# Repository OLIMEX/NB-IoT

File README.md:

# NB-IoT
NB-IoT is LPWAN technology for IoT with many advantages over LoRa and SigFox.

NB-IoT technology works over existing GSM network. This means all existing GSM networks with LTE can support NB-IoT if the protocol is installed by your GSM operator.
One base cell can talk up to 100 000 NB-IoT nodes. One base cell can establish connection in urban area 1-10km and in rural area 10-100km
One NB-IoT node can last on battery up to 10 years if less 200 bytes per day are transmitted

# NB-IoT-DevKit board has these features:
- BC-66 all world wide GSM bands coverage
- NB-IoT 25.5 kbps up and down link
- Ultra low power design
- Build in Li-Po battery charger
- Nano SIM
- Level shifters for 5x GPIOs, I2C, SPI, UART
- Micro UEXT connector
- U.FL antenna connector
- Status LEDs
- Dimensions 40x25 mm

# License
- Hardware is with CERN OHL v1.2 license
- Software is with GPL3 license
- Documentation is with CC BY-SA 4.0 license

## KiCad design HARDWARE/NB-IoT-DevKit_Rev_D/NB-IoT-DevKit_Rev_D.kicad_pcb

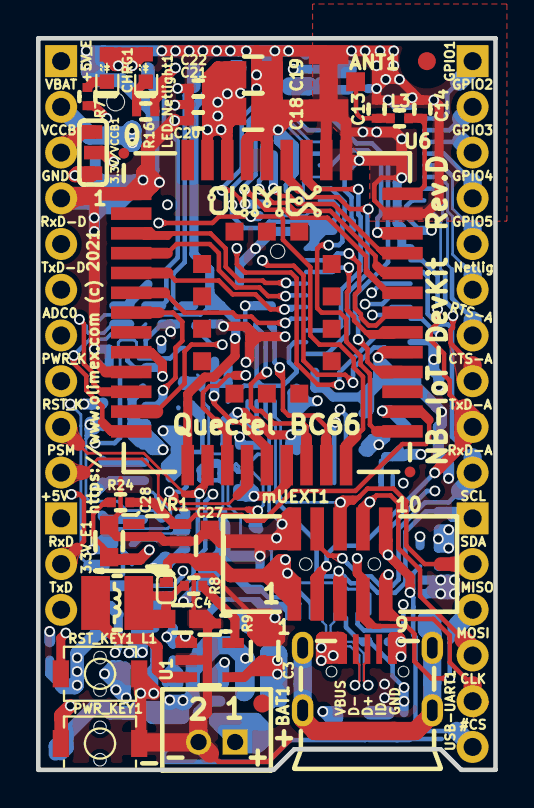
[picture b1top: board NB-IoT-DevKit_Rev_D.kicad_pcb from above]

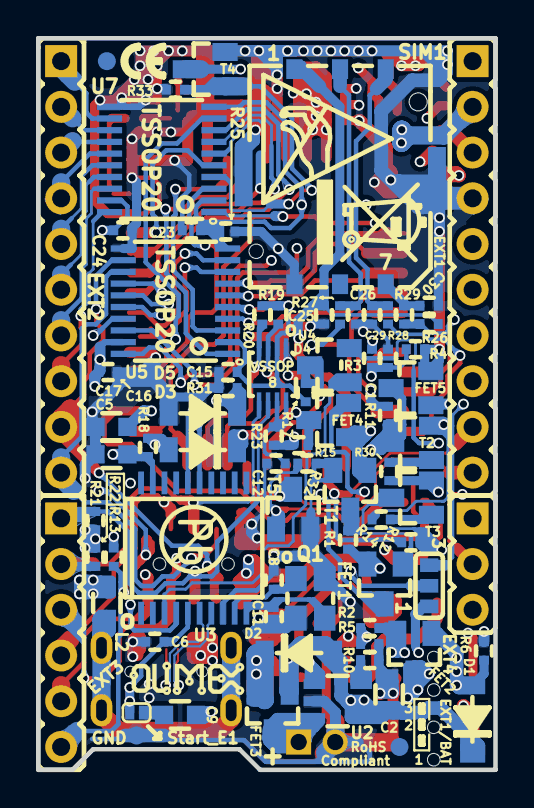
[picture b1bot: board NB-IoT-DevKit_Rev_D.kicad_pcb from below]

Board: 4 copper layers, 25.4 x 40.6 mm, 116 parts (82 on the bottom side), 93 nets.

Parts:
3.3V/VCCB1: Soldered/Opened; SJ_2_SMALL
3.3V_E1: Soldered; SJ_1_SMALLER
ANT1: U.FL-R-SMT-1
BAT1: DW02S; LIPO_BAT_VERTICAL_DW02S
BAT/EXT1: BAT:Soldered/EXT:Opened; SJ_2_SMALL
C1: 1nF/50V/10%/X7R/C0402; C_0402_5MIL_DWS
C2, C3, C4, C5, C9, C27, C28: 22uF/6.3V/20%/X5R/C0603; C_0603_5MIL_DWS
C6, C12, C15, C16, C20, C23, C24, C25: 100nF/10V/10%/X5R/C0402; C_0402_5MIL_DWS
C8, C11: 27pF/50V/5%/C0G/C0402; C_0402_5MIL_DWS
C13, C14, C22: NA/C0402; C_0402_5MIL_DWS
C17: 4.7uF/6.3V/20%/X5R/C0603; C_0603_5MIL_DWS
C18, C19: 47uF/6.3V/20%/X5R/C0805; C_0805_5MIL_DWS
C21, C26, C29, C30: 33pF/50V/5%/COG/C0402; C_0402_5MIL_DWS
CHRG1: LED/YELLOW/0603; LED_0603_KA
D1, D2, D3, D5: 1N5819S4/SOD123; SOD-123_1C-2A_KA
D4: BAT54A(SOT23-3); SOT23-3
EXT1, EXT2: HN1x10
EXT3: HN1x6
EXT4: HN1x3
FET1, FET2, FET3: WPM2015-3/TR; SOT23
FET4, FET5: BSS138(SOT23-3); SOT23
FID1, FID2, FID3, FID4: Fiducial; Fiducial1x3
GND_Pin1: TESTPAD; TESTPAD_40-ROUND
L1: 2.2uH/1.5A/DCR=72mR/20%/3.00x3.00x1.50mm/CD32(NR3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; CD32
L2: FB0603/600R/200mA(160808-601); L_0603_5MIL_DWS
L3: 0R/R0402; L_0402_5MIL_DWS
LED_Netlight1: LED/Green/0603; LED_0603_KA
Logo_OLimeX: LOGO_OLIMEX_80
Olimex_Logo1: LOGO_OLIMEX_80
PWR_KEY1: IT1185AU2; IT1185AU2_V2
Q1: Q12MHz/20pF/10ppm/4P/3.2x2.5mm; TSX-3.2x2.5mm_GND(3)
R1, R31: 100k/R0402; R_0402_5MIL_DWS
R2, R3, R13, R25, R32, R33: 1M/R0402; R_0402_5MIL_DWS
R4, R5: 470k/R0402; R_0402_5MIL_DWS
R6, R16, R26: 10k/R0402; R_0402_5MIL_DWS
R7, R10: 2.2k/R0402; R_0402_5MIL_DWS
R8, R23: 220k/R0402; R_0402_5MIL_DWS
R9: 49.9k/1%/R0402; R_0402_5MIL_DWS
R11, R12: 100R/R0402; R_0402_5MIL_DWS
R14, R17, R19, R20, R30: 1.5k/R0402; R_0402_5MIL_DWS
R15, R18, R21, R22: 4.7k/R0402; R_0402_5MIL_DWS
R24: NA/R0402; R_0402_5MIL_DWS
R27, R28, R29: 22R/R0402; R_0402_5MIL_DWS
RST_KEY1: IT1185AU2; IT1185AU2_V2
SIM1: SIMNANO-6P-1.3H
Sign_Antistatic: Val**; LOGO_ANTISTATIC_1
Sign_CE_Small: CE_Sign_Small
Sign_PbFree: LOGO_PBFREE
Sign_RecycleBin: LOGO_RECYCLEBIN_1
Start_E1: Soldered; SJ_1_SMALLER
T1, T4, T5: BSS138(SOT23-3); SOT23
T2, T3: BC817(SOT23-3); SOT23
U1: SY8089AAAC(SOT23-5); SOT-23-5
U2: BL4054B-42TPRN(SOT23-5); SOT-23-5
U3: CH340T(SSOP20W); SSOP-20W
U4: PCA9306DCUR(VSSOP-8); VSSOP-8_Pitch-0.50mm_Pad-0.25mm_Dimensions-2.30x2.00x1.00mm
U5, U7: TXB0108PWR(TSSOP-20); TSSOP20_Pitch-0.65mm_6.6x4.5x1.2mm
U6: Quectel_NB-IoT_BC66_Module(Pinout-OpenCPU); Quectel_NB-IoT_BC66_Module-17.7mmx15.8mmx2.0mm
USB-UART1: MISB-SWMM-5B-LF(USB_MICRO); USB-MICRO_MISB-SWMM-5B_LF
VR1: AP1231-1.8V(SOT23-5); SOT-23-5
mUEXT1: HAB-VCR-010-LF

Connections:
+1.8V: C15.2, C23.2, C28.1, FET4.1, R17.2, R19.2, R20.2, R24.2, R25.2, T1.1, U4.2, U5.2, U5.10, U7.2, U7.10, VR1.5
+3V3: 3.3V/VCCB1.3, 3.3V_E1.1, C5.1, C6.1, C18.1, C19.1, C20.1, C21.1, C22.1, C27.1, R13.2, R18.1, Start_E1.2, U3.5, U3.19, U6.42, U6.43, VR1.1, mUEXT1.1
+5V: C2.1, CHRG1.2, D1.1, D2.2, EXT4.1, FET2.2, FET3.1, LED_Netlight1.2, R2.1, U2.4
+5V_EXT: D1.2, EXT1.1, FET2.1, R6.2
+5V_USB: FET2.3, USB-UART1.1
/ADC0: C1.1, R3.2, R4.1, U6.9
/ADC0toEXT: BAT/EXT1.3, EXT1.7
/CH340(TxD): D4.1, U3.3
/CTS-AUX: EXT2.8, U7.20
/CTS_AUX\PWR-SENS: R2.2, R5.1, U6.22, U7.1
/DTR: R30.1, T3.2, U3.15
/GPIO1: EXT2.1, U7.12
/GPIO1(EINT): U6.26, U7.9
/GPIO2: EXT2.2, U7.13
/GPIO2(EINT): U6.30, U7.8
/GPIO3: EXT2.3, U7.14
/GPIO3(PWM3): U6.31, U7.7
/GPIO4: EXT2.4, U7.15
/GPIO4(EINT): U6.32, U7.6
/GPIO5: EXT2.5, U7.16
/GPIO5(EINT): U6.33, U7.5
/I2C0-SCL(RI): EXT3.1, R21.1, U4.6, mUEXT1.5
/I2C0-SDA(DCD): EXT3.2, R22.1, U4.5, mUEXT1.6
/I2C0_SCL(EINT): R19.1, U4.3, U6.20
/I2C0_SDA(EINT): R20.1, U4.4, U6.21
/Netlight: EXT2.6, U7.17
/Netlight(PWM0): R33.1, T4.1, U6.16, U7.4
/PSM_EINT: T5.3, U6.19
/PSM_EINTn: EXT1.10, R32.1, T5.1
/PWR_KEY: EXT1.8, R11.1, U6.7
/RST_KEY: EXT1.9, R12.1, U6.15
/RTS: R14.1, T2.2, U3.16
/RTS-AUX: EXT2.7, U7.18
/RTS_AUX(PWM2): U6.23, U7.3
/RxD: D3.1, EXT4.2, FET4.3, R15.1
/RxD-AUX: EXT2.10, U5.13, mUEXT1.4
/RxD-DBG: EXT1.5, U5.18
/RxD_AUX(EINT): U5.8, U6.28
/RxD_DBG(EINT): U5.3, U6.38
/RxD_MAIN: D4.3, R17.1, U6.18
/SIM_CLK: R28.2, U6.13
/SIM_DATA: R26.2, R29.2, U6.11
/SIM_RST: R27.2, U6.12
/SIM_VDD: C25.1, R26.1, SIM1.1, U6.14
/SPI-CS: EXT3.6, R13.1, U5.17, mUEXT1.10
/SPI-MISO: EXT3.3, U5.14, mUEXT1.7
/SPI-MOSI: EXT3.4, U5.15, mUEXT1.8
/SPI-SCLK: EXT3.5, U5.16, mUEXT1.9
/SPI_CS(EINT): U5.4, U6.6
/SPI_MISO(EINT): U5.7, U6.3
/SPI_MOSI(EINT): U5.6, U6.4
/SPI_SCLK(EINT): U5.5, U6.5
/TxD: D4.2, EXT4.3
/TxD-AUX: EXT2.9, U5.12, mUEXT1.3
/TxD-DBG: EXT1.6, U5.20
/TxD_AUX(EINT): U5.9, U6.29
/TxD_DBG(EINT): U5.1, U6.39
/TxD_MAIN: FET4.2, U6.17
/USB_D+: U3.6, USB-UART1.3
/USB_D-: U3.7, USB-UART1.2
/VCCB: C16.2, C24.2, FET1.3, R15.2, R21.2, R22.2, R23.2, U5.19, U7.19
/VCCB(3.3V): 3.3V/VCCB1.1, EXT1.3
GND: ANT1.2, BAT1.2, C1.2, C2.2, C3.2, C4.2, C5.2, C6.2, C8.2, C11.2, C12.2, C13.1, C14.1, C15.1, C16.1, C17.1, C18.2, C19.2, C20.2, C21.2, C22.2, C23.1, C24.1, C25.2, C26.1, C27.2, C28.2, C29.1, C30.1, D5.2, EXT1.4, FET5.2, GND_Pin1.1, L2.2, PWR_KEY1.2, Q1.3, R4.2, R5.2, R6.1, R9.2, R10.2, R25.1, R31.1, R32.2, R33.2, RST_KEY1.2, SIM1.0, SIM1.5, T1.2, T4.2, T5.2, U1.2, U2.2, U3.8, U4.1, U5.11, U6.1, U6.10, U6.27, U6.34, U6.36, U6.37, U6.40, U6.41, U7.11, USB-UART1.5, VR1.2, mUEXT1.2
unnamed: 3.3V/VCCB1.2, FET1.2, R1.1
unnamed: 3.3V_E1.2, C4.1, L1.2, R8.2
unnamed: ANT1.1, C13.2, L3.2
unnamed: BAT/EXT1.2, R3.1
unnamed: C3.1, D2.1, FET3.2, U1.1, U1.4
unnamed: C8.1, Q1.1, U3.9
unnamed: C9.1, Start_E1.1
unnamed: C9.2, D5.1, FET5.1, R31.2
unnamed: C11.1, Q1.2, U3.10
unnamed: C12.1, R23.1, U4.7, U4.8
unnamed: C14.2, L3.1, U6.35
unnamed: C26.2, R27.1, SIM1.2
unnamed: C29.2, R28.1, SIM1.3
unnamed: C30.2, R29.1, SIM1.7
unnamed: CHRG1.1, R7.1
unnamed: D3.2, R18.2, U3.4
unnamed: FET1.1, R1.2, T1.3
unnamed: FET5.3, PWR_KEY1.1, R11.2, T2.3
unnamed: L1.1, U1.3
unnamed: L2.1, USB-UART1.0
unnamed: LED_Netlight1.1, R16.1
unnamed: R7.2, U2.1
unnamed: R8.1, R9.1, U1.5
unnamed: R10.1, U2.5
unnamed: R12.2, RST_KEY1.1, T3.3
unnamed: R14.2, T3.1
unnamed: R16.2, T4.3
unnamed: R30.2, T2.1
VBAT: BAT1.1, BAT/EXT1.1, EXT1.2, FET3.3, U2.3
VDD_1.8V: C17.2, R24.1, U6.24, VR1.3

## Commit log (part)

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2019-10-17 initial upload of hardware and software files
2019-10-30 update
    link to FTP firmware
2019-10-30 update
    update
2019-10-30 update
    fixed markdown
2019-12-09 Create AT_example
2019-12-09 Update AT_example
2019-12-17 New
    Added at restore tool
2020-01-02 .sh files are now executable
2020-01-03 Fixed color binding
2020-06-19 Update
    Added docs for buffers
2022-11-16 Update
    Updated pictures
2024-01-04 Update
    Added hardware revisions C and D and hardware revision changes.

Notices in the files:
HARDWARE/NB-IoT-DevKit_Rev_D/NB-IoT-DevKit_Rev_D.kicad_pcb:
https://www.olimex.com (c) 2021
